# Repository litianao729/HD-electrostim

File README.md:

# A scalable, non-invasive, high-frequency stimulator for tactile sensory feedback

# Description
This project is used to support the thesis and paper. A scalable, non-invasive, high-frequency stimulator is developed in this work for tactile sensory feedback. The hardware design files, and software program files are contained in this GitHub project.
# Instruction
The folder named pcb contains three folders which correspond to three separate PCB boards of the stimulator. For each folder, the file with extension of .kicad_pro can be opened by KiCad software. One can modify the schematics and PCB layouts for a specific PCB design project. To utilize the design:
1.	Find the folder has “gerber” in its name. This folder contains the information to fabricate the board. 
2.	Upload that folder (or compress before uploading) to a PCB fabrication server such as PCBway. 
3.	Assemble the boards according to the components listed in the table with an extension name of .csv.
Software program codes to control the stimulator are saved in the rest folders. Folders named whole_time_current_pulse and whole_time_voltage_pulse only has Arduino IDE sketch. These sketches are example codes to run the stimulator producing endless square waveform with constant current or voltage amplitude. To utilize these codes:
1.	Download the entire folder and open the sketch (extension name is .ino) via Arduino IDE.
2.	Upload the sketch to the stimulator (connected with your laptop).
3.	Measure the signal from the electrode outputs (align with the settings in the sketch).
Folder named switching_speed_test only has Arduino sketch. This sketch is used to test the switch speed of the electrode switchboard of the stimulator. To utilize this code:
1.	Download the entire folder and open the sketch (extension name is .ino) via Arduino IDE.
2.	Upload the sketch to the stimulator (connected with your laptop).
3.	Measure the signal from the electrode outputs (align with the settings in the sketch) with a oscilloscope to observe the time delay between electrode disconnection and reconnection (electrode switching event is defined as a disconnection of the old electrode and a connection of another electrode)
Other folders contain not only Arduino IDE sketch but also MATLAB script (extension name: .m) or live script (extension name: .mlx). The MATLAB scripts determine the values of the parameters defined in the Arduino IDE sketches. By serial communication, these values are transferred to the IDE interface. For each folder, to utilize the codes:
Download the folder. Open the Arduino IDE sketch and MATLAB script with Arduino IDE and MATLAB respectively.
Upload the sketch to the stimulator (connected with your laptop).
Run the first section in the MATLAB script (to establish serial communication between MATLAB and Arduino IDE).
If there is no error, run the rest sections of the script.
For live script, interactive controls are used to define the parameter values. One can change the values as the program is running.

# Notifications and troubleshooting:
The connection between MATLAB and Arduino IDE is achieved through serial communication. When using MATLAB script as the parameter inputs, you cannot use Serial monitor tool of the Arduino IDE.
Sometimes error might occur when running the first section of the MATLAB script to establish serial communication. To solve this issue, you can check if serial monitor tool is being used and reupload the sketch.

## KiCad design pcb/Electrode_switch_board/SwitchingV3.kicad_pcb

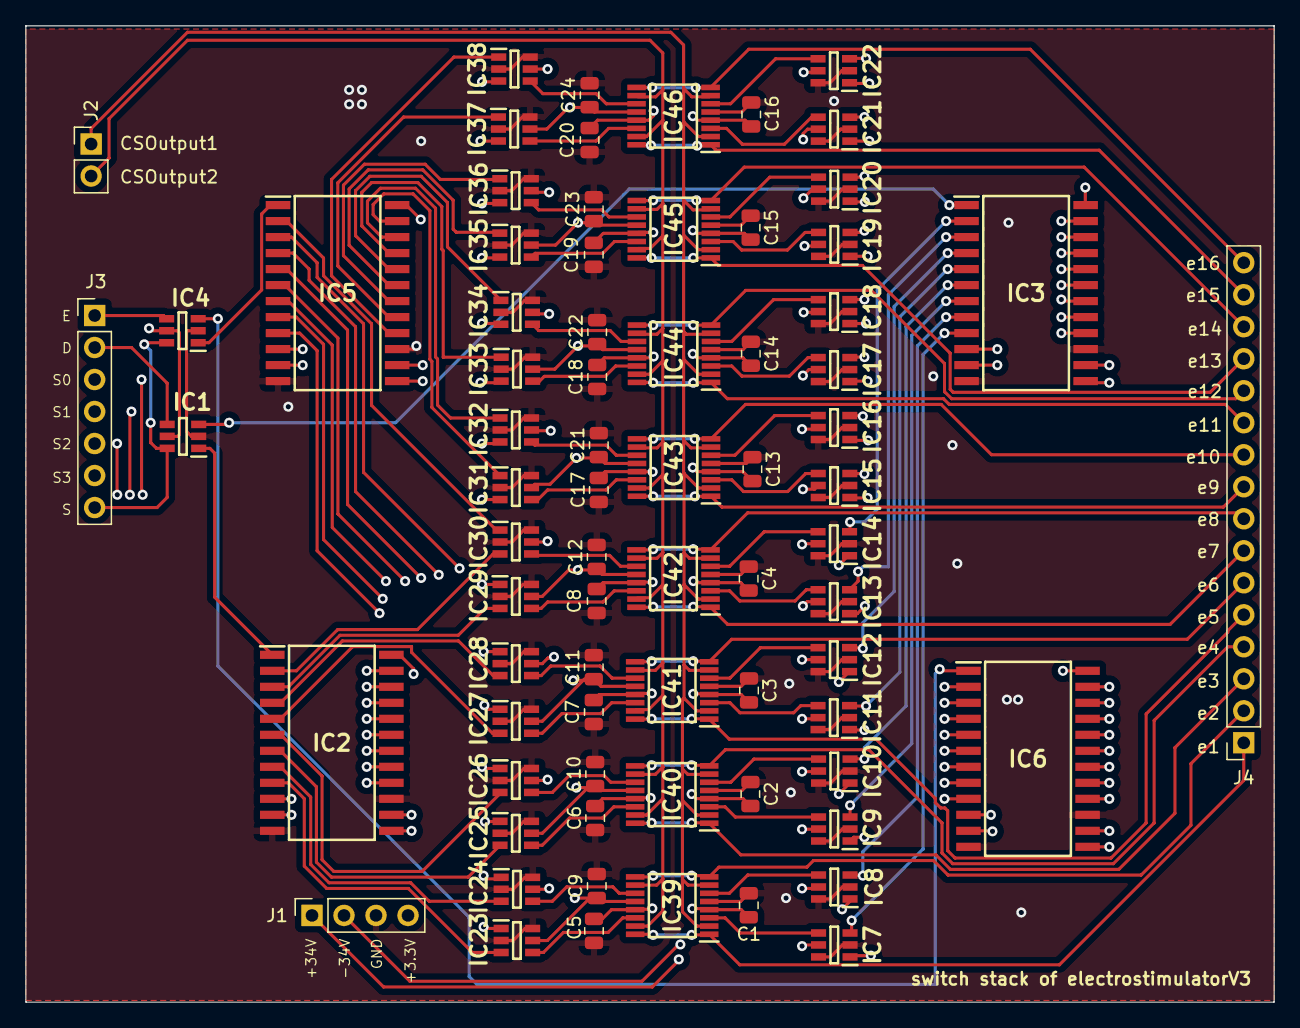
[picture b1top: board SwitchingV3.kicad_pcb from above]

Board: 4 copper layers, 99.1 x 77.5 mm, 74 parts (0 on the bottom side), 129 nets.

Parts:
C1, C2, C3, C4, C5, C6, C7, C8, C9, C10, C11, C12, C13, C14, C15, C16, C17, C18, C19, C20, C21, C22, C23, C24: 1uF; C_0805_2012Metric
IC1, IC4: SN74LVC1G3157DBVR; SOT95P280X145-6N
IC2, IC3, IC5, IC6: CD74HC4067M; SOIC127P1030X265-24N
IC7, IC8, IC9, IC10, IC11, IC12, IC13, IC14, IC15, IC16, IC17, IC18, IC19, IC20, IC21, IC22, IC23, IC24, IC25, IC26, IC27, IC28, IC29, IC30, IC31, IC32, IC33, IC34, IC35, IC36, IC37, IC38: 74LVC1G373DBVRE4; SOT95P280X145-6N
IC39, IC40, IC41, IC42, IC43, IC44, IC45, IC46: MAX14757EUE+T; SOP65P640X110-16N
J1: Conn_01x04_Socket; PinSocket_1x04_P2.54mm_Vertical
J2: Conn_01x02_Socket; PinHeader_1x02_P2.54mm_Vertical
J3: Conn_01x07_Socket; PinHeader_1x07_P2.54mm_Vertical
J4: Conn_01x16_Pin; PinSocket_1x16_P2.54mm_Vertical

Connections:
+3.3V: C9.1, C10.1, C11.1, C12.1, C21.1, C22.1, C23.1, C24.1, IC1.5 (VCC), IC2.24 (VCC), IC3.24 (VCC), IC4.5 (VCC), IC5.24 (VCC), IC6.24 (VCC), IC7.5 (VCC), IC8.5 (VCC), IC9.5 (VCC), IC10.5 (VCC), IC11.5 (VCC), IC12.5 (VCC), IC13.5 (VCC), IC14.5 (VCC), IC15.5 (VCC), IC16.5 (VCC), IC17.5 (VCC), IC18.5 (VCC), IC19.5 (VCC), IC20.5 (VCC), IC21.5 (VCC), IC22.5 (VCC), IC23.5 (VCC), IC24.5 (VCC), IC25.5 (VCC), IC26.5 (VCC), IC27.5 (VCC), IC28.5 (VCC), IC29.5 (VCC), IC30.5 (VCC), IC31.5 (VCC), IC32.5 (VCC), IC33.5 (VCC), IC34.5 (VCC), IC35.5 (VCC), IC36.5 (VCC), IC37.5 (VCC), IC38.5 (VCC), IC39.12 (VL), IC40.12 (VL), IC41.12 (VL), IC42.12 (VL), IC43.12 (VL), IC44.12 (VL), IC45.12 (VL), IC46.12 (VL), J1.4
+34V: C5.1, C6.1, C7.1, C8.1, C17.1, C18.1, C19.1, C20.1, IC39.13 (VDD), IC40.13 (VDD), IC41.13 (VDD), IC42.13 (VDD), IC43.13 (VDD), IC44.13 (VDD), IC45.13 (VDD), IC46.13 (VDD), J1.1
-34V: C1.1, C2.1, C3.1, C4.1, C13.1, C14.1, C15.1, C16.1, IC39.4 (VSS), IC40.4 (VSS), IC41.4 (VSS), IC42.4 (VSS), IC43.4 (VSS), IC44.4 (VSS), IC45.4 (VSS), IC46.4 (VSS), J1.2
CSOutput1: IC39.2 (B1), IC39.7 (B4), IC40.2 (B1), IC40.7 (B4), IC41.2 (B1), IC41.7 (B4), IC42.2 (B1), IC42.7 (B4), IC43.2 (B1), IC43.7 (B4), IC44.2 (B1), IC44.7 (B4), IC45.2 (B1), IC45.7 (B4), IC46.2 (B1), IC46.7 (B4), J2.1
CSOutput2: IC39.10 (B3), IC39.15 (B2), IC40.10 (B3), IC40.15 (B2), IC41.10 (B3), IC41.15 (B2), IC42.10 (B3), IC42.15 (B2), IC43.10 (B3), IC43.15 (B2), IC44.10 (B3), IC44.15 (B2), IC45.10 (B3), IC45.15 (B2), IC46.10 (B3), IC46.15 (B2), J2.2
D1_1: IC3.9 (I0), IC7.3 (D)
D1_2: IC2.9 (I0), IC23.3 (D)
D2_1: IC3.8 (I1), IC8.3 (D)
D2_2: IC2.8 (I1), IC24.3 (D)
D3_1: IC3.7 (I2), IC9.3 (D)
D3_2: IC2.7 (I2), IC25.3 (D)
D4_1: IC3.6 (I3), IC10.3 (D)
D4_2: IC2.6 (I3), IC26.3 (D)
D5_1: IC3.5 (I4), IC11.3 (D)
D5_2: IC2.5 (I4), IC27.3 (D)
D6_1: IC3.4 (I5), IC12.3 (D)
D6_2: IC2.4 (I5), IC28.3 (D)
D7_1: IC3.3 (I6), IC13.3 (D)
D7_2: IC2.3 (I6), IC29.3 (D)
D8_1: IC3.2 (I7), IC14.3 (D)
D8_2: IC2.2 (I7), IC30.3 (D)
D9_1: IC3.23 (I8), IC15.3 (D)
D9_2: IC2.23 (I8), IC31.3 (D)
D10_1: IC3.22 (I9), IC16.3 (D)
D10_2: IC2.22 (I9), IC32.3 (D)
D11_1: IC3.21 (I10), IC17.3 (D)
D11_2: IC2.21 (I10), IC33.3 (D)
D12_1: IC3.20 (I11), IC18.3 (D)
D12_2: IC2.20 (I11), IC34.3 (D)
D13_1: IC3.19 (I12), IC19.3 (D)
D13_2: IC2.19 (I12), IC35.3 (D)
D14_1: IC3.18 (I13), IC20.3 (D)
D14_2: IC2.18 (I13), IC36.3 (D)
D15_1: IC3.17 (I14), IC21.3 (D)
D15_2: IC2.17 (I14), IC37.3 (D)
D16_1: IC3.16 (I15), IC22.3 (D)
D16_2: IC2.16 (I15), IC38.3 (D)
D_control: IC1.4 (A), J3.2
E1_1: IC6.9 (I0), IC7.1 (LE)
E1_2: IC5.9 (I0), IC23.1 (LE)
E2_1: IC6.8 (I1), IC8.1 (LE)
E2_2: IC5.8 (I1), IC24.1 (LE)
E3_1: IC6.7 (I2), IC9.1 (LE)
E3_2: IC5.7 (I2), IC25.1 (LE)
E4_1: IC6.6 (I3), IC10.1 (LE)
E4_2: IC5.6 (I3), IC26.1 (LE)
E5_1: IC6.5 (I4), IC11.1 (LE)
E5_2: IC5.5 (I4), IC27.1 (LE)
E6_1: IC6.4 (I5), IC12.1 (LE)
E6_2: IC5.4 (I5), IC28.1 (LE)
E7_1: IC6.3 (I6), IC13.1 (LE)
E7_2: IC5.3 (I6), IC29.1 (LE)
E8_1: IC6.2 (I7), IC14.1 (LE)
E8_2: IC5.2 (I7), IC30.1 (LE)
E9_1: IC6.23 (I8), IC15.1 (LE)
E9_2: IC5.23 (I8), IC31.1 (LE)
E10_1: IC6.22 (I9), IC16.1 (LE)
E10_2: IC5.22 (I9), IC32.1 (LE)
E11_1: IC6.21 (I10), IC17.1 (LE)
E11_2: IC5.21 (I10), IC33.1 (LE)
E12_1: IC6.20 (I11), IC18.1 (LE)
E12_2: IC5.20 (I11), IC34.1 (LE)
E13_1: IC6.19 (I12), IC19.1 (LE)
E13_2: IC5.19 (I12), IC35.1 (LE)
E14_1: IC6.18 (I13), IC20.1 (LE)
E14_2: IC5.18 (I13), IC36.1 (LE)
E15_1: IC6.17 (I14), IC21.1 (LE)
E15_2: IC5.17 (I14), IC37.1 (LE)
E16_1: IC6.16 (I15), IC22.1 (LE)
E16_2: IC5.16 (I15), IC38.1 (LE)
E_control: IC4.4 (A), J3.1
GND: C1.2, C2.2, C3.2, C4.2, C5.2, C6.2, C7.2, C8.2, C9.2, C10.2, C11.2, C12.2, C13.2, C14.2, C15.2, C16.2, C17.2, C18.2, C19.2, C20.2, C21.2, C22.2, C23.2, C24.2, IC1.2 (GND), IC2.12 (GND), IC2.15 (~E), IC3.12 (GND), IC3.15 (~E), IC4.2 (GND), IC5.12 (GND), IC5.15 (~E), IC6.12 (GND), IC6.15 (~E), IC7.2 (GND), IC7.6 (~OE), IC8.2 (GND), IC8.6 (~OE), IC9.2 (GND), IC9.6 (~OE), IC10.2 (GND), IC10.6 (~OE), IC11.2 (GND), IC11.6 (~OE), IC12.2 (GND), IC12.6 (~OE), IC13.2 (GND), IC13.6 (~OE), IC14.2 (GND), IC14.6 (~OE), IC15.2 (GND), IC15.6 (~OE), IC16.2 (GND), IC16.6 (~OE), IC17.2 (GND), IC17.6 (~OE), IC18.2 (GND), IC18.6 (~OE), IC19.2 (GND), IC19.6 (~OE), IC20.2 (GND), IC20.6 (~OE), IC21.2 (GND), IC21.6 (~OE), IC22.2 (GND), IC22.6 (~OE), IC23.2 (GND), IC23.6 (~OE), IC24.2 (GND), IC24.6 (~OE), IC25.2 (GND), IC25.6 (~OE), IC26.2 (GND), IC26.6 (~OE), IC27.2 (GND), IC27.6 (~OE), IC28.2 (GND), IC28.6 (~OE), IC29.2 (GND), IC29.6 (~OE), IC30.2 (GND), IC30.6 (~OE), IC31.2 (GND), IC31.6 (~OE), IC32.2 (GND), IC32.6 (~OE), IC33.2 (GND), IC33.6 (~OE), IC34.2 (GND), IC34.6 (~OE), IC35.2 (GND), IC35.6 (~OE), IC36.2 (GND), IC36.6 (~OE), IC37.2 (GND), IC37.6 (~OE), IC38.2 (GND), IC38.6 (~OE), IC39.5 (GND), IC40.5 (GND), IC41.5 (GND), IC42.5 (GND), IC43.5 (GND), IC44.5 (GND), IC45.5 (GND), IC46.5 (GND), J1.3
unnamed: IC1.3 (B1), IC3.1 (COMMON_INPUT/OUTPUT)
unnamed: IC1.1 (B2), IC2.1 (COMMON_INPUT/OUTPUT)
unnamed: IC4.3 (B1), IC6.1 (COMMON_INPUT/OUTPUT)
unnamed: IC4.1 (B2), IC5.1 (COMMON_INPUT/OUTPUT)
Q1_1: IC7.4 (Q), IC39.3 (EN1)
Q1_2: IC23.4 (Q), IC39.14 (EN2)
Q2_1: IC8.4 (Q), IC39.6 (EN4)
Q2_2: IC24.4 (Q), IC39.11 (EN3)
Q3_1: IC9.4 (Q), IC40.3 (EN1)
Q3_2: IC25.4 (Q), IC40.14 (EN2)
Q4_1: IC10.4 (Q), IC40.6 (EN4)
Q4_2: IC26.4 (Q), IC40.11 (EN3)
Q5_1: IC11.4 (Q), IC41.3 (EN1)
Q5_2: IC27.4 (Q), IC41.14 (EN2)
Q6_1: IC12.4 (Q), IC41.6 (EN4)
Q6_2: IC28.4 (Q), IC41.11 (EN3)
Q7_1: IC13.4 (Q), IC42.3 (EN1)
Q7_2: IC29.4 (Q), IC42.14 (EN2)
Q8_1: IC14.4 (Q), IC42.6 (EN4)
Q8_2: IC30.4 (Q), IC42.11 (EN3)
Q9_1: IC15.4 (Q), IC43.3 (EN1)
Q9_2: IC31.4 (Q), IC43.14 (EN2)
Q10_1: IC16.4 (Q), IC43.6 (EN4)
Q10_2: IC32.4 (Q), IC43.11 (EN3)
Q11_1: IC17.4 (Q), IC44.3 (EN1)
Q11_2: IC33.4 (Q), IC44.14 (EN2)
Q12_1: IC18.4 (Q), IC44.6 (EN4)
Q12_2: IC34.4 (Q), IC44.11 (EN3)
Q13_1: IC19.4 (Q), IC45.3 (EN1)
Q13_2: IC35.4 (Q), IC45.14 (EN2)
Q14_1: IC20.4 (Q), IC45.6 (EN4)
Q14_2: IC36.4 (Q), IC45.11 (EN3)
Q15_1: IC21.4 (Q), IC46.3 (EN1)
Q15_2: IC37.4 (Q), IC46.14 (EN2)
Q16_1: IC22.4 (Q), IC46.6 (EN4)
Q16_2: IC38.4 (Q), IC46.11 (EN3)
S: IC1.6 (S), IC4.6 (S), J3.7
S0: IC2.10 (S0), IC3.10 (S0), IC5.10 (S0), IC6.10 (S0), J3.3
S1: IC2.11 (S1), IC3.11 (S1), IC5.11 (S1), IC6.11 (S1), J3.4
S2: IC2.14 (S2), IC3.14 (S2), IC5.14 (S2), IC6.14 (S2), J3.5
S3: IC2.13 (S3), IC3.13 (S3), IC5.13 (S3), IC6.13 (S3), J3.6
e1: IC39.1 (A1), IC39.16 (A2), J4.1
e2: IC39.8 (A4), IC39.9 (A3), J4.2
e3: IC40.1 (A1), IC40.16 (A2), J4.3
e4: IC40.8 (A4), IC40.9 (A3), J4.4
e5: IC41.1 (A1), IC41.16 (A2), J4.5
e6: IC41.8 (A4), IC41.9 (A3), J4.6
e7: IC42.1 (A1), IC42.16 (A2), J4.7
e8: IC42.8 (A4), IC42.9 (A3), J4.8
e9: IC43.1 (A1), IC43.16 (A2), J4.9
e10: IC43.8 (A4), IC43.9 (A3), J4.10
e11: IC44.1 (A1), IC44.16 (A2), J4.11
e12: IC44.8 (A4), IC44.9 (A3), J4.12
e13: IC45.1 (A1), IC45.16 (A2), J4.13
e14: IC45.8 (A4), IC45.9 (A3), J4.14
e15: IC46.1 (A1), IC46.16 (A2), J4.15
e16: IC46.8 (A4), IC46.9 (A3), J4.16

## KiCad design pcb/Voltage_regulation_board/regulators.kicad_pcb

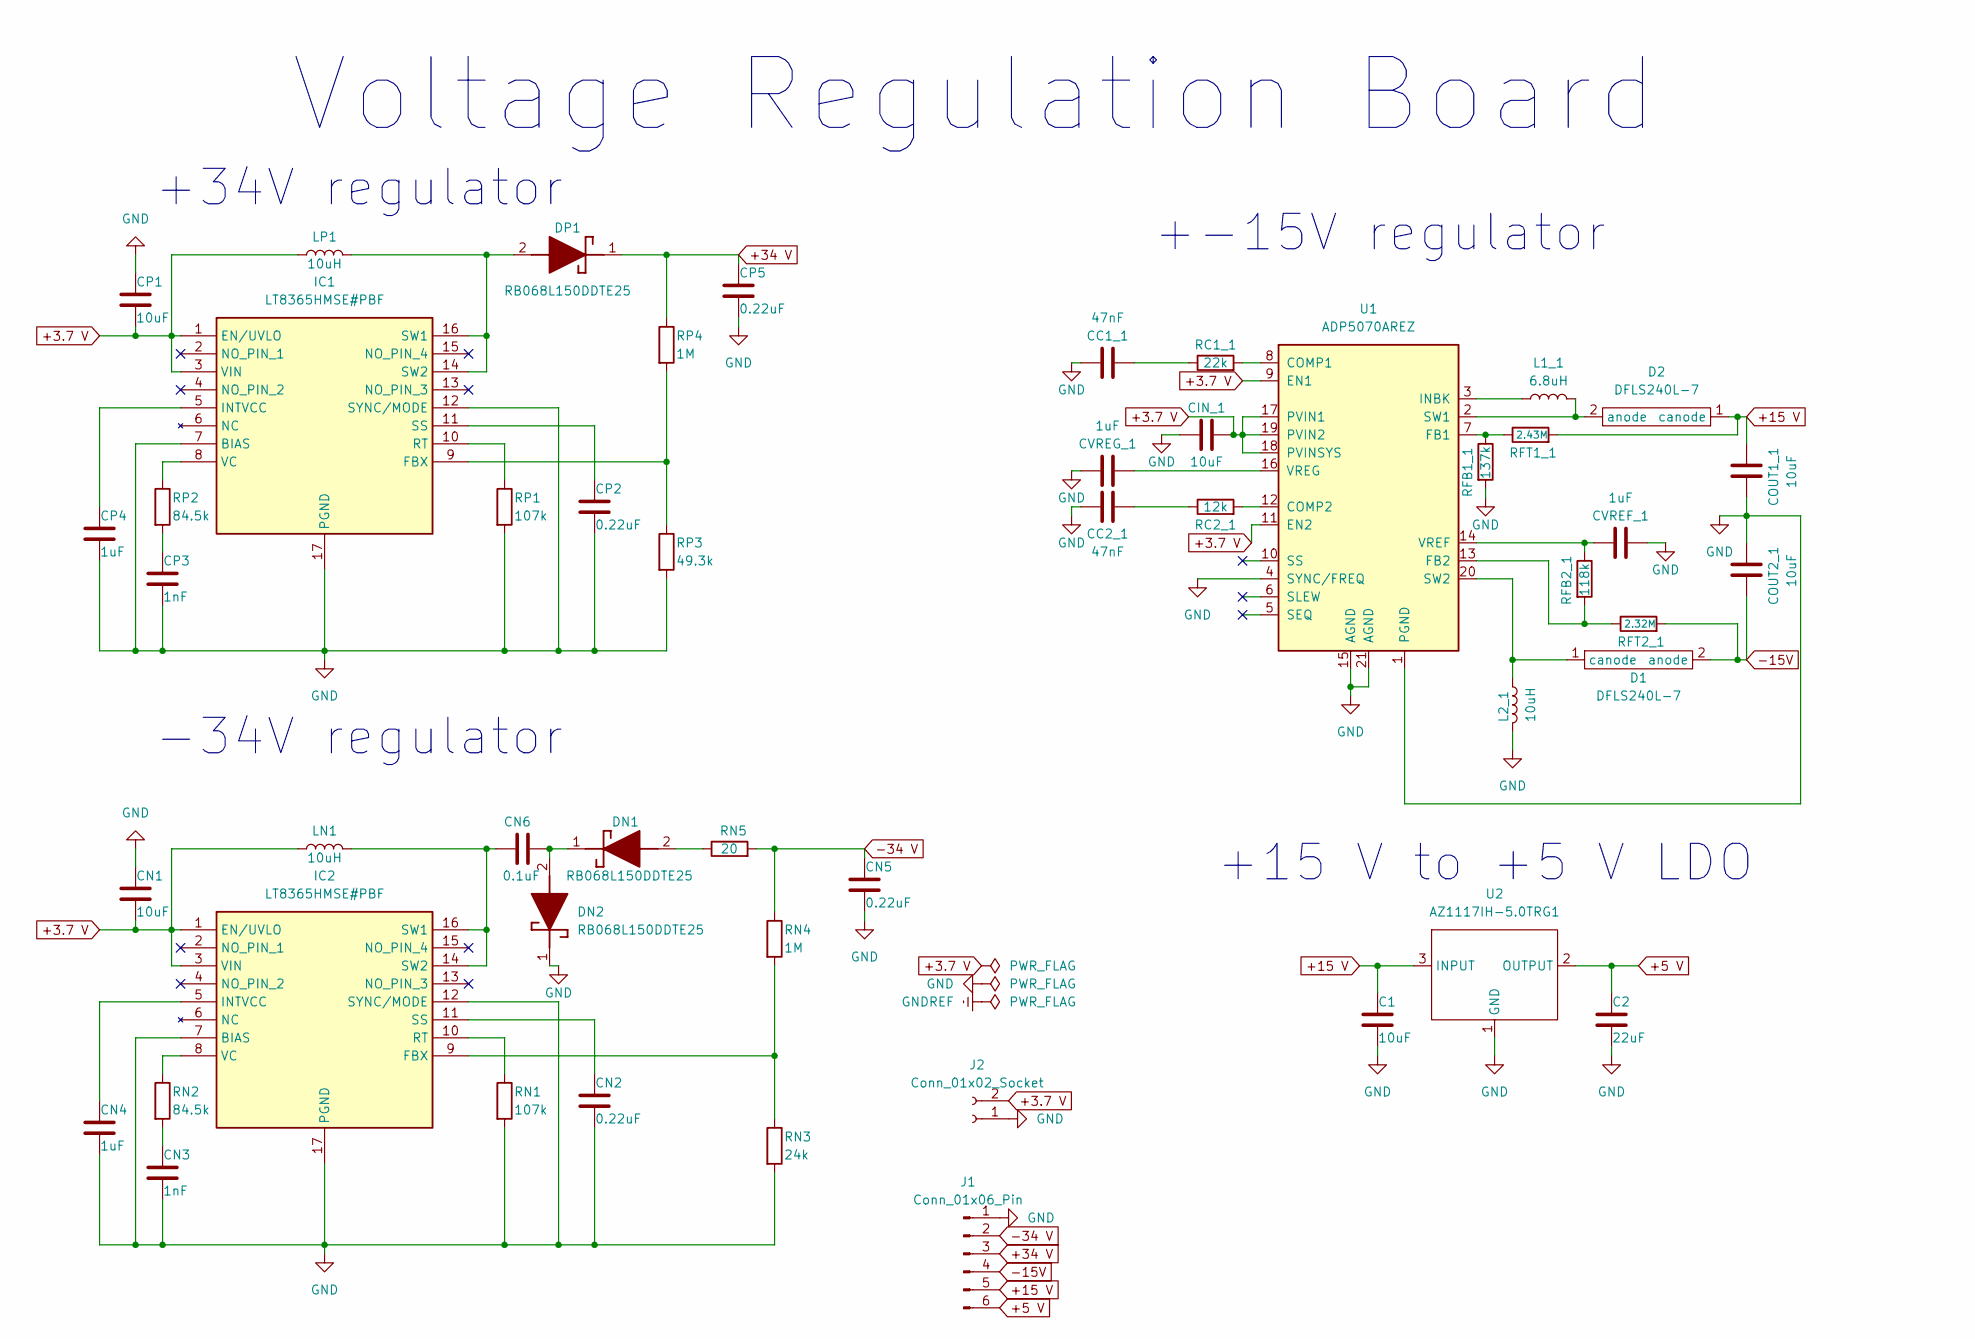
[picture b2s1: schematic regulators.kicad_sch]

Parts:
C1: 10uF; C_1210_3225Metric_Pad1.33x2.70mm_HandSolder
C2: 22uF; C_0805_2012Metric_Pad1.18x1.45mm_HandSolder
CC1_1, CC2_1: 47nF; C_0805_2012Metric_Pad1.18x1.45mm_HandSolder
CIN_1: 10uF; C_1210_3225Metric_Pad1.33x2.70mm_HandSolder
CN1: 10uF; C_1210_3225Metric_Pad1.33x2.70mm_HandSolder
CN2, CN5: 0.22uF; C_0805_2012Metric_Pad1.18x1.45mm_HandSolder
CN3: 1nF; C_0805_2012Metric_Pad1.18x1.45mm_HandSolder
CN4: 1uF; C_0805_2012Metric_Pad1.18x1.45mm_HandSolder
CN6: 0.1uF; C_0805_2012Metric_Pad1.18x1.45mm_HandSolder
COUT1_1, COUT2_1: 10uF; C_1210_3225Metric_Pad1.33x2.70mm_HandSolder
CP1: 10uF; C_1210_3225Metric_Pad1.33x2.70mm_HandSolder
CP2, CP5: 0.22uF; C_0805_2012Metric_Pad1.18x1.45mm_HandSolder
CP3: 1nF; C_0805_2012Metric_Pad1.18x1.45mm_HandSolder
CP4: 1uF; C_0805_2012Metric_Pad1.18x1.45mm_HandSolder
CVREF_1: 1uF; C_0805_2012Metric_Pad1.18x1.45mm_HandSolder
CVREG_1: 1uF; C_0805_2012Metric_Pad1.18x1.45mm_HandSolder
D1, D2: DFLS240L-7; D_PowerDI-123
DN1, DN2: RB068L150DDTE25; DIOM5026X220N; Mouser Part Number 755-RB068L150DDTE25
DP1: RB068L150DDTE25; DIOM5026X220N; Mouser Part Number 755-RB068L150DDTE25
IC1, IC2: LT8365HMSE#PBF; SOP50P490X110-17N; Mouser Part Number 584-LT8365HMSE#PBF
J1: Conn_01x06_Pin; PinHeader_1x06_P2.54mm_Horizontal
J2: Conn_01x02_Socket; PinSocket_1x02_P2.54mm_Horizontal
L1_1: 6.8uH; L_Coilcraft_XAL4040-XXX
L2_1: 10uH; L_Coilcraft_XAL4040-XXX
LN1: 10uH; L_Coilcraft_XAL4040-XXX
LP1: 10uH; L_Coilcraft_XAL4040-XXX
RC1_1: 22k; R_0805_2012Metric_Pad1.20x1.40mm_HandSolder
RC2_1: 12k; R_0805_2012Metric_Pad1.20x1.40mm_HandSolder
RFB1_1: 137k; R_0805_2012Metric_Pad1.20x1.40mm_HandSolder
RFB2_1: 118k; R_0805_2012Metric_Pad1.20x1.40mm_HandSolder
RFT1_1: 2.43M; R_0805_2012Metric_Pad1.20x1.40mm_HandSolder
RFT2_1: 2.32M; R_0805_2012Metric_Pad1.20x1.40mm_HandSolder
RN1: 107k; R_0805_2012Metric_Pad1.20x1.40mm_HandSolder
RN2: 84.5k; R_0805_2012Metric_Pad1.20x1.40mm_HandSolder
RN3: 24k; R_0805_2012Metric_Pad1.20x1.40mm_HandSolder
RN4: 1M; R_0805_2012Metric_Pad1.20x1.40mm_HandSolder
RN5: 20; R_0805_2012Metric_Pad1.20x1.40mm_HandSolder
RP1: 107k; R_0805_2012Metric_Pad1.20x1.40mm_HandSolder
RP2: 84.5k; R_0805_2012Metric_Pad1.20x1.40mm_HandSolder
RP3: 49.3k; R_0805_2012Metric_Pad1.20x1.40mm_HandSolder
RP4: 1M; R_0805_2012Metric_Pad1.20x1.40mm_HandSolder
U1: ADP5070AREZ; ETSSOP-20-1EP_4.4x6.5mm_P0.65mm_EP3x4.2mm
U2: AZ1117IH-5.0TRG1; SOT-223-3_TabPin2

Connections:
+3.7 V: CIN_1.2, CN1.2, CP1.2, IC1.1 (EN/UVLO), IC1.3 (VIN), IC2.1 (EN/UVLO), IC2.3 (VIN), J2.2, LN1.1, LP1.1, U1.9 (EN1), U1.11 (EN2), U1.17 (PVIN1), U1.18 (PVINSYS), U1.19 (PVIN2)
+5 V: C2.1, J1.6, U2.2 (OUTPUT)
+15 V: C1.1, COUT1_1.1, D2.1 (canode), J1.5, RFT1_1.2, U2.3 (INPUT)
+34 V: CP5.1, DP1.1 (K), J1.3, RP4.1
-15V: COUT2_1.2, D1.2 (anode), J1.4, RFT2_1.2
-34 V: CN5.1, J1.2, RN4.1, RN5.2
GND: C1.2, C2.2, CC1_1.1, CC2_1.1, CIN_1.1, CN1.1, CN2.2, CN3.2, CN4.2, CN5.2, COUT1_1.2, COUT2_1.1, CP1.1, CP2.2, CP3.2, CP4.2, CP5.2, CVREF_1.2, CVREG_1.1, DN2.1 (K), IC1.7 (BIAS), IC1.12 (SYNC/MODE), IC1.17 (PGND), IC2.7 (BIAS), IC2.12 (SYNC/MODE), IC2.17 (PGND), J1.1, J2.1, L2_1.2, RFB1_1.2, RN1.2, RN3.2, RP1.2, RP3.2, U1.1 (PGND), U1.4 (SYNC/FREQ), U1.15 (AGND), U1.21 (AGND), U2.1 (GND)
unnamed: CC1_1.2, RC1_1.1
unnamed: CC2_1.2, RC2_1.1
unnamed: CN3.1, RN2.2
unnamed: CP3.1, RP2.2
unnamed: D1.1 (canode), L2_1.1, U1.20 (SW2)
unnamed: D2.2 (anode), L1_1.2, U1.2 (SW1)
unnamed: DN1.2 (A), RN5.1
unnamed: CN6.2, DN1.1 (K), DN2.2 (A)
unnamed: DP1.2 (A), IC1.14 (SW2), IC1.16 (SW1), LP1.2
unnamed: IC1.9 (FBX), RP3.1, RP4.2
unnamed: CP4.1, IC1.5 (INTVCC)
unnamed: IC1.10 (RT), RP1.1
unnamed: CP2.1, IC1.11 (SS)
unnamed: IC1.8 (VC), RP2.1
unnamed: IC2.9 (FBX), RN3.1, RN4.2
unnamed: CN4.1, IC2.5 (INTVCC)
unnamed: IC2.10 (RT), RN1.1
unnamed: CN2.1, IC2.11 (SS)
unnamed: CN6.1, IC2.14 (SW2), IC2.16 (SW1), LN1.2
unnamed: IC2.8 (VC), RN2.1
unnamed: RC1_1.2, U1.8 (COMP1)
unnamed: RC2_1.2, U1.12 (COMP2)
unnamed: RFB1_1.1, RFT1_1.1, U1.7 (FB1)
unnamed: RFB2_1.2, RFT2_1.1, U1.13 (FB2)
unnamed: L1_1.1, U1.3 (INBK)
unnamed: CVREF_1.1, RFB2_1.1, U1.14 (VREF)
unnamed: CVREG_1.2, U1.16 (VREG)

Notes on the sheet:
Voltage Regulation Board
+34V regulator
+-15V regulator
-34V regulator
+15 V to +5 V LDO

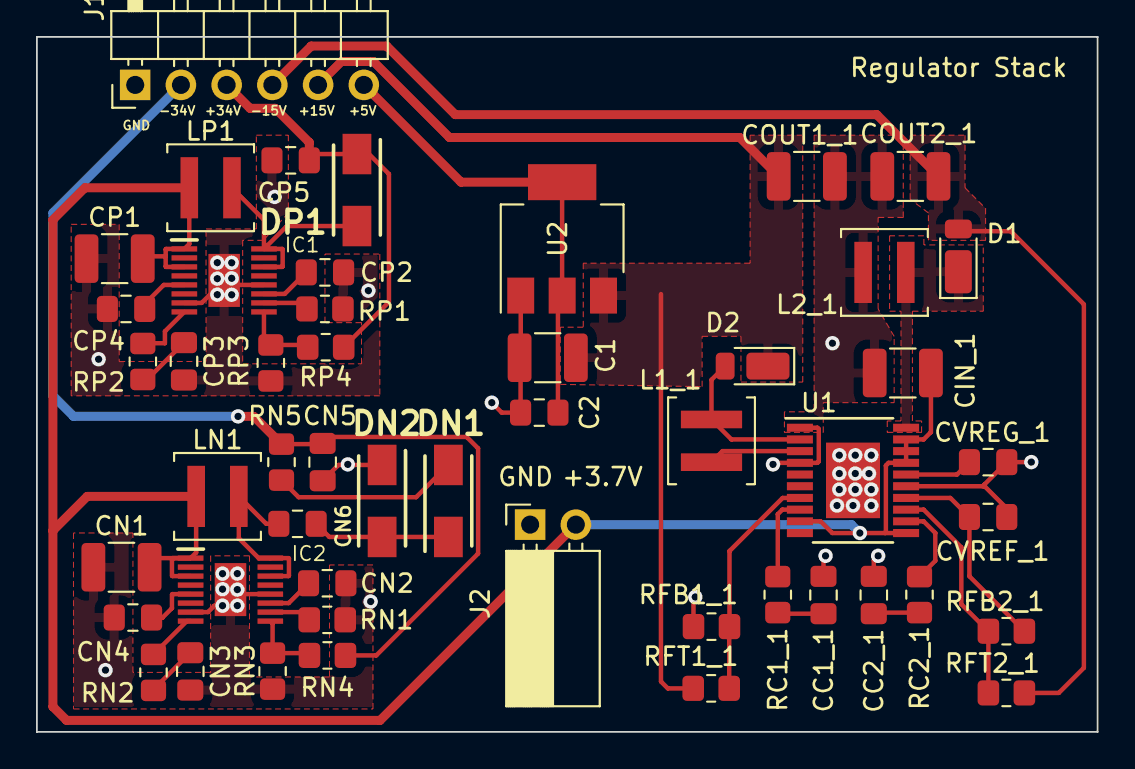
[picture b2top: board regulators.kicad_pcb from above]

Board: 2 copper layers, 58.9 x 38.6 mm, 50 parts (0 on the bottom side), 34 nets.

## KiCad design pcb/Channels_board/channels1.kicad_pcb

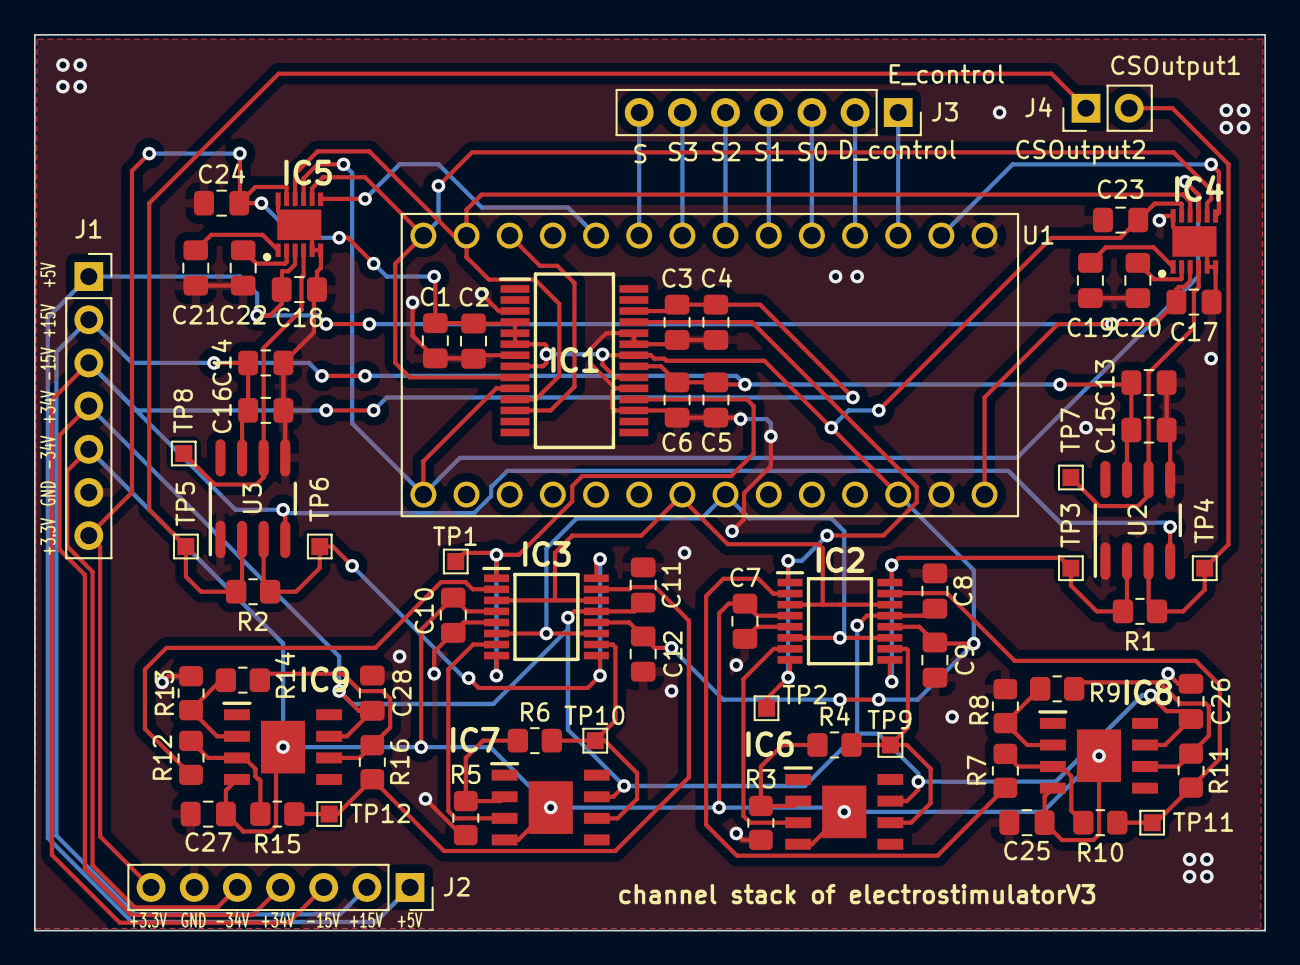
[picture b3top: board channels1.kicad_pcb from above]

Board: 2 copper layers, 72.4 x 52.7 mm, 72 parts (0 on the bottom side), 50 nets.

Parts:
C1, C3, C5, C20, C22: 10uF; C_0805_2012Metric_Pad1.18x1.45mm_HandSolder
C2, C4, C6, C17, C18, C19, C21, C23, C24: 0.1uF; C_0805_2012Metric_Pad1.18x1.45mm_HandSolder
C7, C8, C9, C10, C11, C12, C13, C14: 1uF; C_0805_2012Metric_Pad1.18x1.45mm_HandSolder
C15, C16: 100 nF; C_0805_2012Metric_Pad1.18x1.45mm_HandSolder
C25, C26, C27, C28: 100nF; C_0805_2012Metric_Pad1.18x1.45mm_HandSolder
IC1: MAX5322EAI+; SOP65P778X199-28N
IC2, IC3: MAX14757EUE+T; SOP65P640X110-16N
IC4, IC5: MAX11156ETC+; SON50P300X300X80-13N
IC6, IC7, IC8, IC9: OPA455IDDA; SOIC127P600X170-9N
J1, J2, J3: Conn_01x07_Socket; PinSocket_1x07_P2.54mm_Vertical
J4: Conn_01x02_Pin; PinHeader_1x02_P2.54mm_Vertical
R1, R2: 240; R_0805_2012Metric_Pad1.20x1.40mm_HandSolder
R3, R5: 10k; R_0805_2012Metric_Pad1.20x1.40mm_HandSolder
R4, R6: 50k; R_0805_2012Metric_Pad1.20x1.40mm_HandSolder
R7, R12: 101k; R_0805_2012Metric_Pad1.20x1.40mm_HandSolder
R8, R9, R10, R13, R14, R15: 100k; R_0805_2012Metric_Pad1.20x1.40mm_HandSolder
R11, R16: 1k; R_0805_2012Metric_Pad1.20x1.40mm_HandSolder
TP1, TP2, TP3, TP4, TP5, TP6, TP7, TP8, TP9, TP10, TP11, TP12: TestPoint; TestPoint_Pad_1.0x1.0mm
U1: DEV-15583; MODULE_DEV-15583
U2, U3: INA149AID; D0008A_N

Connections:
+3.3V: C1.2, C2.2, C9.2, C12.2, C23.2, C24.2, IC1.4 (~SHDN), IC1.5 (~LDAC), IC1.6 (~CLR), IC1.8 (VCC), IC1.20 (REFA), IC1.22 (REFB), IC2.12 (VL), IC3.12 (VL), IC4.11 (OVDD), IC5.11 (OVDD), J1.7, J2.7, U1.3.3V_2
+5 V: C17.2, C18.2, IC4.3 (VDD), IC5.3 (VDD), J1.1, J2.1, U1.VIN
+15V: C5.1, C6.1, C13.1, C14.1, C15.1, C16.1, IC1.21 (VDD), J1.2, J2.2, U2.7 (V+), U3.7 (V+)
+34 V: C8.2, C11.2, C26.1, C28.1, IC2.13 (VDD), IC3.13 (VDD), IC6.7 (V+), IC7.7 (V+), IC8.7 (V+), IC9.7 (V+), J1.4, J2.4
-15V: C3.2, C4.2, IC1.26 (VSS), J1.3, J2.3, U2.4 (V-), U3.4 (V-)
-34 V: C7.2, C10.2, C25.1, C27.1, IC2.4 (VSS), IC3.4 (VSS), IC6.4 (V-), IC6.9 (EP), IC7.4 (V-), IC7.9 (EP), IC8.4 (V-), IC8.9 (EP), IC9.4 (V-), IC9.9 (EP), J1.5, J2.5
CSOutput1: J4.2, R1.2, TP4.1, U2.3 (IN+)
CSOutput2: J4.1, R2.1, TP5.1, U3.2 (IN-)
CSR_V1: IC4.4 (AIN+), TP7.1, U2.6 (VOUT)
CSR_V2: IC5.4 (AIN+), TP8.1, U3.6 (VOUT)
CsADC1: IC4.7 (CNVST), U1.0
CsADC2: IC5.7 (CNVST), U1.8
CsDAC: IC1.12 (~CS), U1.10
DAC Out 1: IC1.25 (OUTB), IC2.1 (A1), IC2.8 (A4), TP2.1
DAC Out 2: IC1.18 (OUTA), IC3.1 (A1), IC3.8 (A4), TP1.1
D_control: J3.2, U1.2
Din: IC1.11 (DIN), IC4.10 (DIN), IC5.10 (DIN), U1.11
Dout: IC1.9 (DOUT), IC4.8 (DOUT), IC5.8 (DOUT), U1.12
E_control: J3.1, U1.1
GND: C1.1, C2.1, C3.1, C4.1, C5.2, C6.2, C7.1, C8.1, C9.1, C10.1, C11.1, C12.1, C13.2, C14.2, C15.2, C16.2, C17.1, C18.1, C19.1, C20.1, C21.1, C22.1, C23.1, C24.1, C25.2, C26.2, C27.2, C28.2, IC1.3 (UNI/~BIPB), IC1.7 (DGND), IC1.17 (UNI/~BIPA), IC1.19 (SGNDA), IC1.23 (AGND), IC1.24 (SGNDB), IC2.5 (GND), IC3.5 (GND), IC4.5 (AIN-), IC4.6 (GND_1), IC4.12 (AGNDS), IC4.13 (GND_2), IC5.5 (AIN-), IC5.6 (GND_1), IC5.12 (AGNDS), IC5.13 (GND_2), J1.6, J2.6, R3.2, R5.2, R8.1, R13.1, U1.G1, U1.G3, U2.1 (REFB), U2.5 (REFA), U3.1 (REFB), U3.5 (REFA)
IO1: IC2.15 (B2), R10.2, R11.2, TP11.1
IO2: IC3.15 (B2), R15.2, R16.2, TP12.1
Input1: IC2.7 (B4), IC6.3 (+IN)
Input2: IC3.7 (B4), IC7.3 (+IN)
unnamed: C20.2, IC4.2 (REF)
unnamed: C19.2, IC4.1 (REFIO)
unnamed: C22.2, IC5.2 (REF)
unnamed: C21.2, IC5.1 (REFIO)
unnamed: IC6.2 (-IN), R3.1, R4.1
unnamed: IC7.2 (-IN), R5.1, R6.1
unnamed: IC8.3 (+IN), R7.2, R10.1
unnamed: IC8.2 (-IN), R8.2, R9.1
unnamed: IC8.6 (OUT), R9.2, R11.1
unnamed: IC9.3 (+IN), R12.2, R15.1
unnamed: IC9.2 (-IN), R13.2, R14.1
unnamed: IC9.6 (OUT), R14.2, R16.1
Output1: IC2.10 (B3), IC6.6 (OUT), R4.2, TP9.1
Output2: IC3.10 (B3), IC7.6 (OUT), R6.2, TP10.1
REF1: IC2.2 (B1), R7.1
REF2: IC3.2 (B1), R12.1
S: J3.7, U1.7
S0: J3.3, U1.3
S1: J3.4, U1.4
S2: J3.5, U1.5
S3: J3.6, U1.6
Sclk: IC1.10 (SCLK), IC4.9 (SCLK), IC5.9 (SCLK), U1.13
channel1: IC2.9 (A3), IC2.16 (A2), R1.1, TP3.1, U2.2 (IN-)
channel2: IC3.9 (A3), IC3.16 (A2), R2.2, TP6.1, U3.3 (IN+)
current mode: IC2.3 (EN1), IC2.14 (EN2), IC3.3 (EN1), IC3.14 (EN2), U1.19
voltage mode: IC2.6 (EN4), IC2.11 (EN3), IC3.6 (EN4), IC3.11 (EN3), U1.20

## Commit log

2024-04-19 add pcb design files
2024-04-19 add whole-time pulse arduino IDE sketches
2024-04-19 update gitignore
2024-04-19 add code for arbitrary waveform
2024-04-19 add code for real-time control
2024-04-19 add code to evaluate switch speed
2024-04-19 add code amplitude modulation
